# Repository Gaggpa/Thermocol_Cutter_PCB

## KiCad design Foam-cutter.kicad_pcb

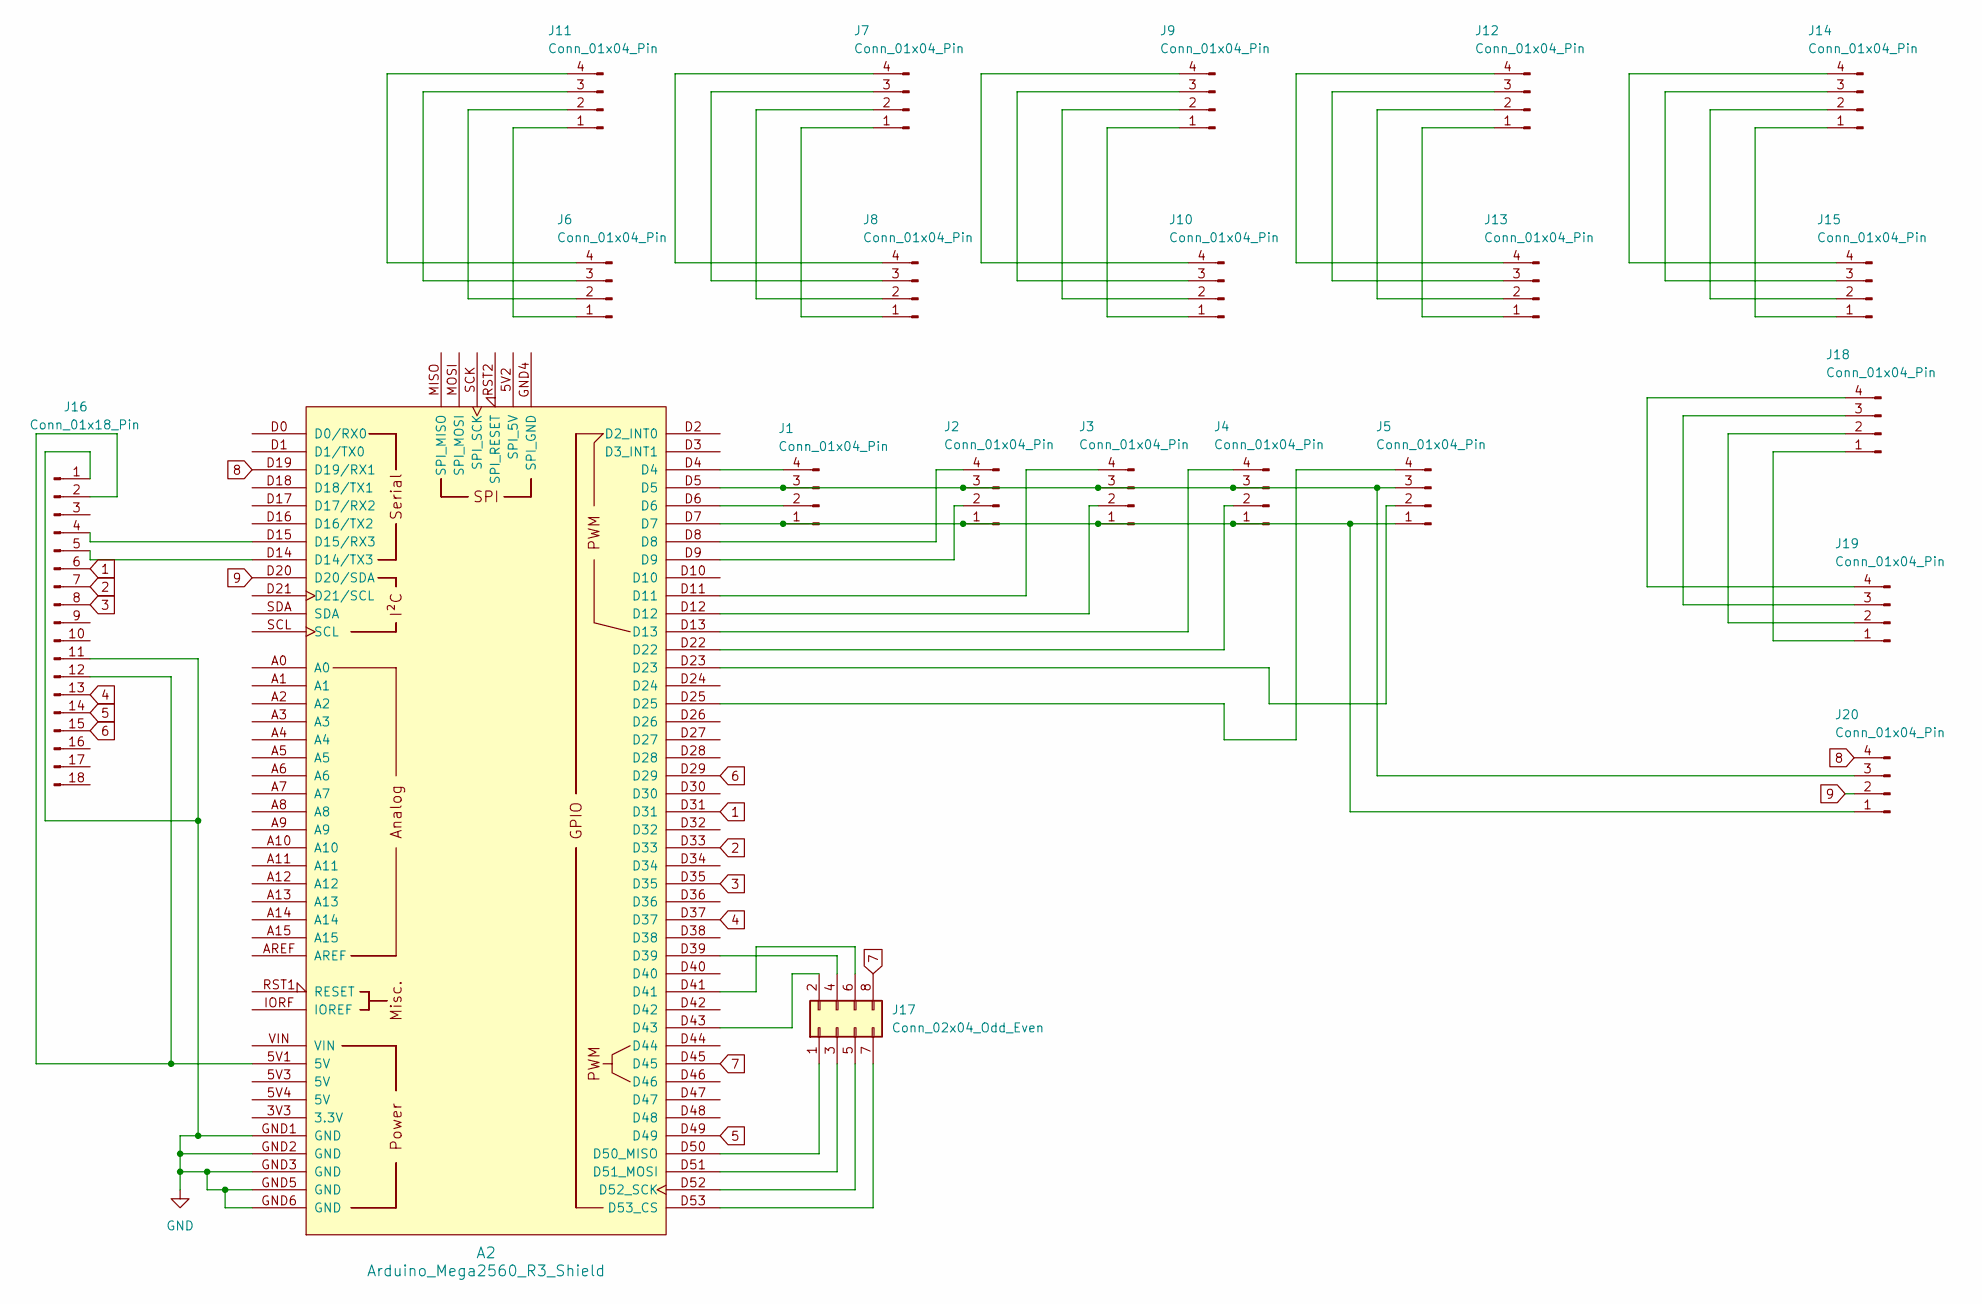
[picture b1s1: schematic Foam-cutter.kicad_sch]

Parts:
A2: Arduino_Mega2560_R3_Shield
J1, J2, J3, J4, J5, J6, J8, J10, J13, J15, J19, J20: Conn_01x04_Pin; PhoenixContact_MCV_1,5_4-G-5.08_1x04_P5.08mm_Vertical
J7, J9, J11, J12, J14, J18: Conn_01x04_Pin; PhoenixContact_MC_1,5_4-G-5.08_1x04_P5.08mm_Horizontal
J16: Conn_01x18_Pin; PinHeader_1x18_P2.54mm_Vertical
J17: Conn_02x04_Odd_Even; PinHeader_2x04_P2.54mm_Vertical

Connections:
1: A2.D31, J16.6
2: A2.D33, J16.7
3: A2.D35, J16.8
4: A2.D37, J16.13
5: A2.D49, J16.14
6: A2.D29, J16.15
7: A2.D45, J17.8
8: A2.D19 (D19/RX1), J20.4
9: A2.D20 (D20/SDA), J20.2
GND: A2.GND1 (GND), A2.GND2 (GND), A2.GND3 (GND), A2.GND5 (GND), A2.GND6 (GND), J16.1, J16.11
unnamed: A2.D14 (D14/TX3), J16.5
unnamed: A2.D15 (D15/RX3), J16.4
unnamed: A2.D50 (D50_MISO), J17.1
unnamed: A2.D51 (D51_MOSI), J17.3
unnamed: A2.D52 (D52_SCK), J17.5
unnamed: A2.D53 (D53_CS), J17.7
unnamed: A2.D7, J1.1, J2.1, J3.1, J4.1, J5.1, J20.1
unnamed: A2.D6, J1.2
unnamed: A2.D5, J1.3, J2.3, J3.3, J4.3, J5.3, J20.3
unnamed: A2.D4, J1.4
unnamed: A2.D9, J2.2
unnamed: A2.D8, J2.4
unnamed: A2.D12, J3.2
unnamed: A2.D11, J3.4
unnamed: A2.D22, J4.2
unnamed: A2.D13, J4.4
unnamed: A2.D23, J5.2
unnamed: A2.D25, J5.4
unnamed: J7.1, J8.1
unnamed: J7.2, J8.2
unnamed: J7.3, J8.3
unnamed: J7.4, J8.4
unnamed: J9.1, J10.1
unnamed: J9.2, J10.2
unnamed: J9.3, J10.3
unnamed: J9.4, J10.4
unnamed: J6.1, J11.1
unnamed: J6.2, J11.2
unnamed: J6.3, J11.3
unnamed: J6.4, J11.4
unnamed: J12.1, J13.1
unnamed: J12.2, J13.2
unnamed: J12.3, J13.3
unnamed: J12.4, J13.4
unnamed: J14.1, J15.1
unnamed: J14.2, J15.2
unnamed: J14.3, J15.3
unnamed: J14.4, J15.4
unnamed: A2.5V1 (5V), J16.2, J16.12
unnamed: A2.D43, J17.2
unnamed: A2.D39, J17.4
unnamed: A2.D41, J17.6
unnamed: J18.1, J19.1
unnamed: J18.2, J19.2
unnamed: J18.3, J19.3
unnamed: J18.4, J19.4

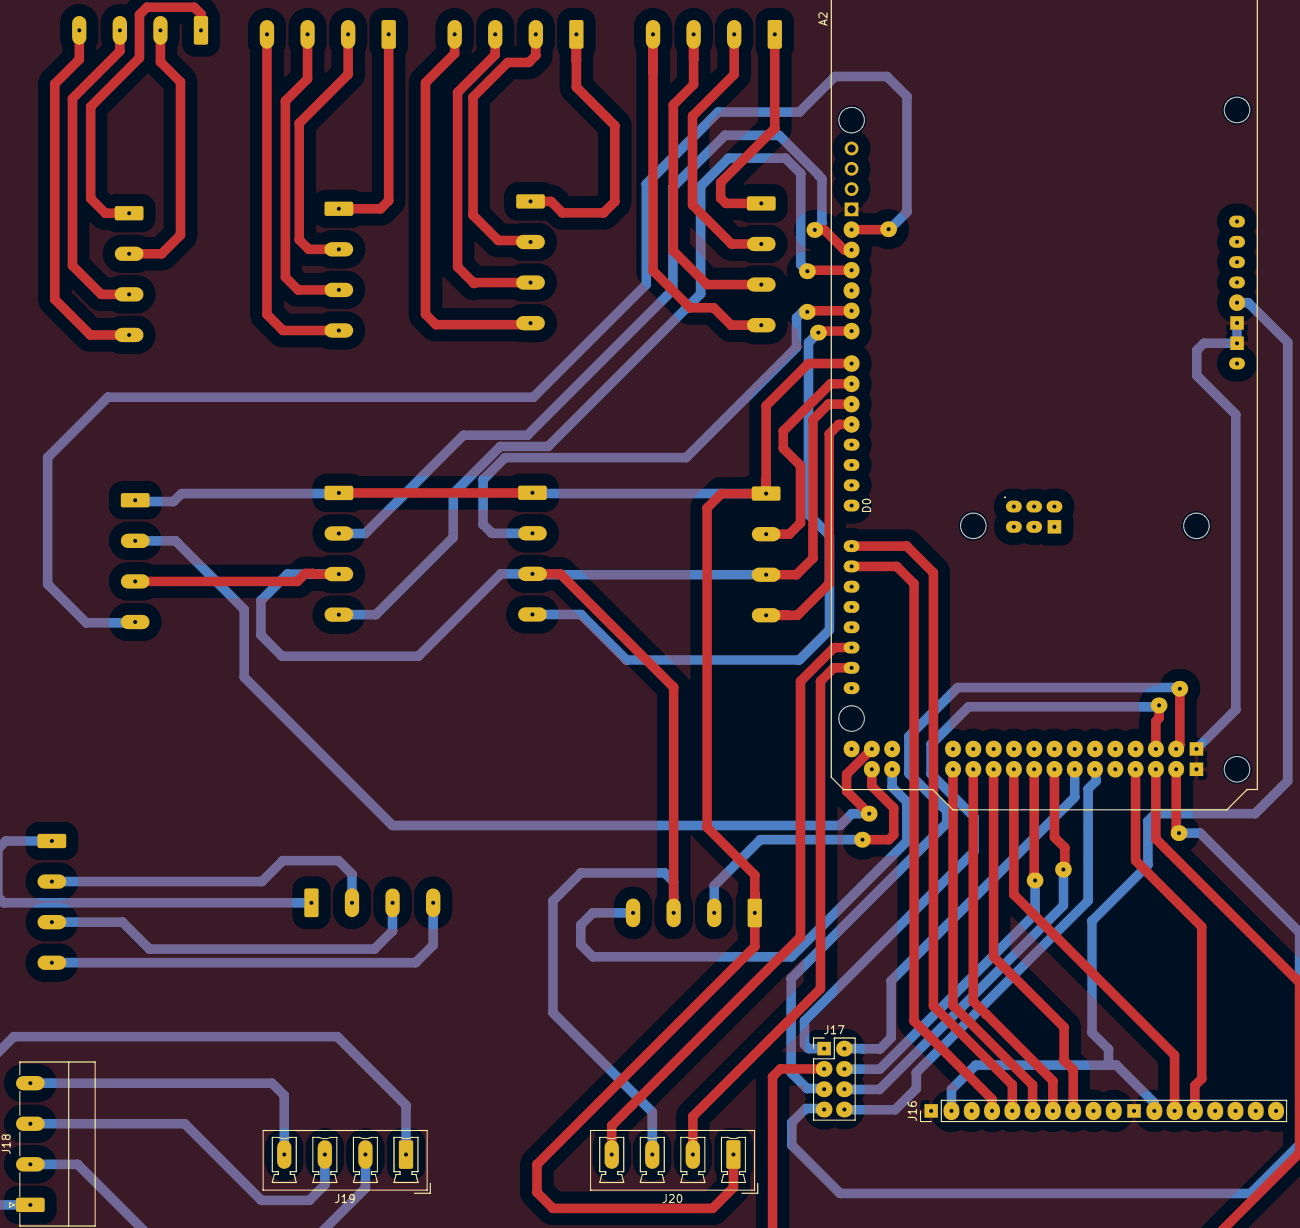
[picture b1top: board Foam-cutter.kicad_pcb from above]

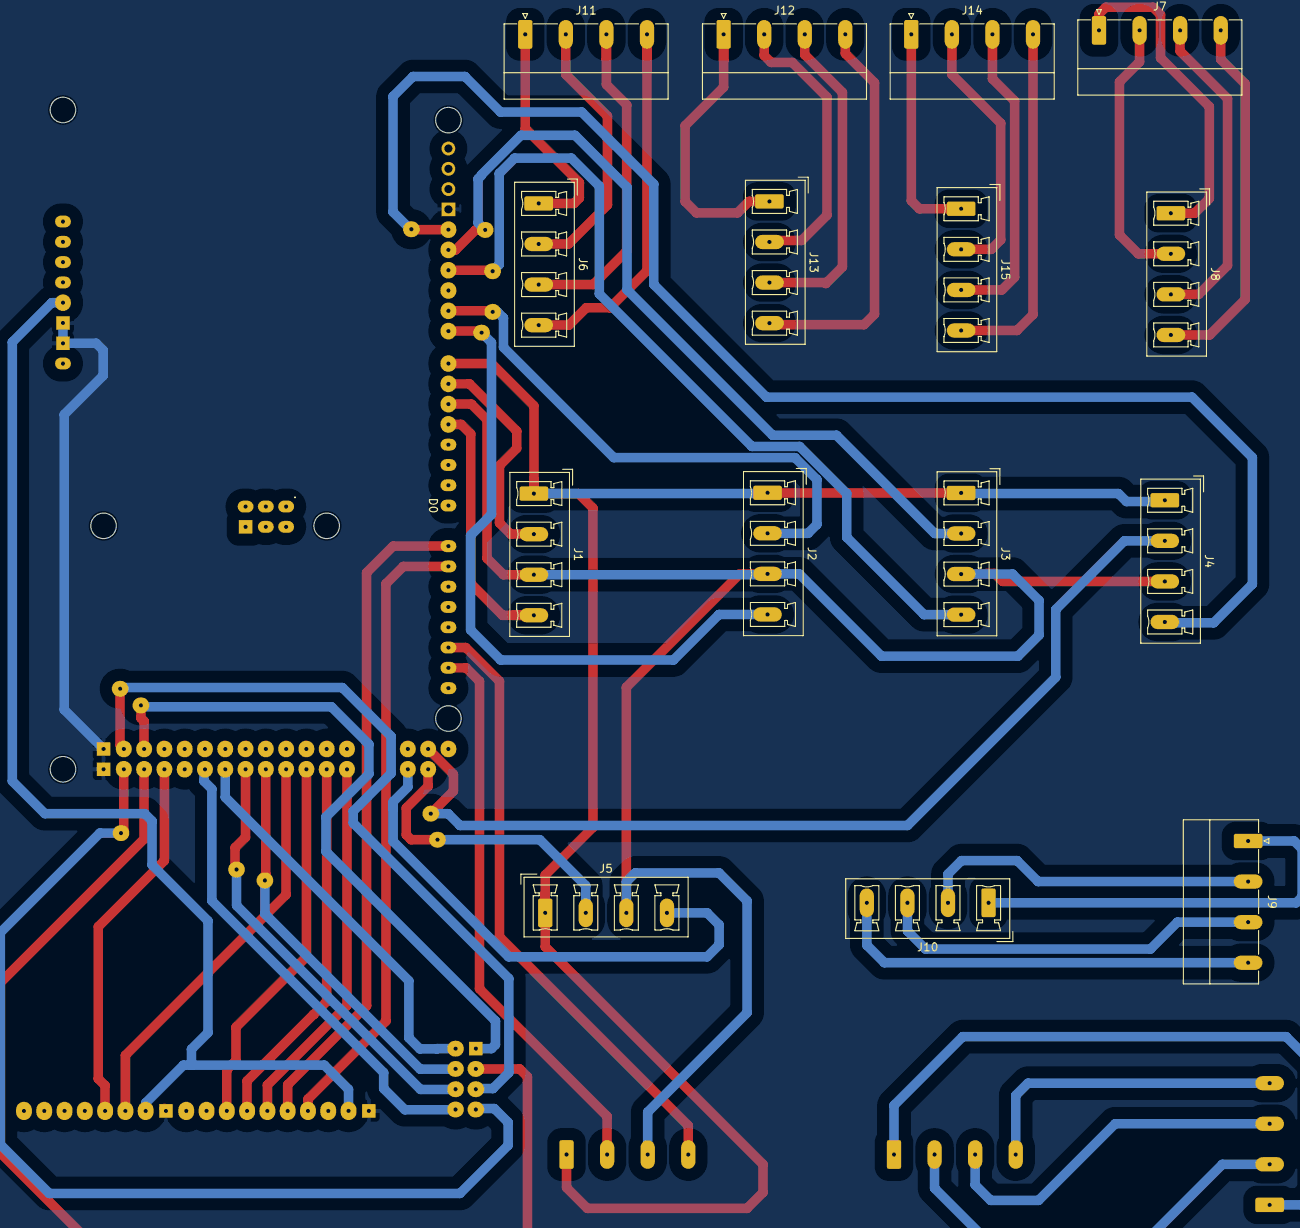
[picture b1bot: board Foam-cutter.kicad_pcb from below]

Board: 2 copper layers, 21 parts (16 on the bottom side), 55 nets.
